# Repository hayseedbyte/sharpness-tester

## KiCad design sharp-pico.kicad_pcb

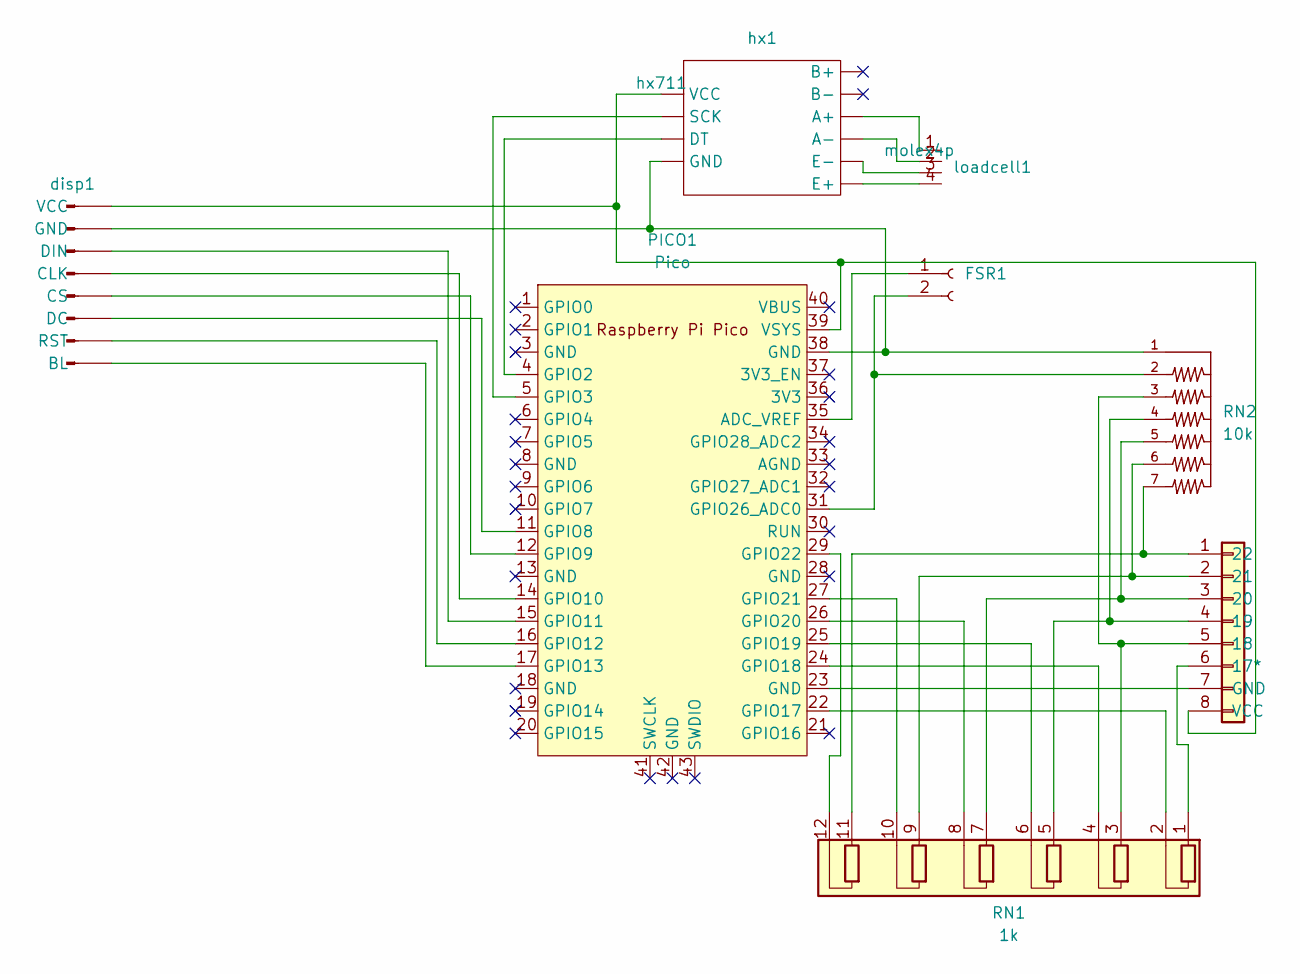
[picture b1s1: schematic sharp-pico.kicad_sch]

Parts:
CNTRL1: Conn_01x08; Molex_KK-254_AE-6410-08A_1x08_P2.54mm_Vertical
FSR1: Conn_01x02_Socket; PinSocket_1x02_P2.54mm_Vertical
PICO1: Pico; RPi_Pico_SMD_TH
RN1: 1k; R_Array_SIP12
RN2: 10k; R_Array_SIP7; PARTREV 09/19
disp1: Conn_01x08_Pin; Molex_KK-254_AE-6410-08A_1x08_P2.54mm_Vertical
hx1: hx711
loadcell1: molex4p; Molex_KK-254_AE-6410-04A_1x04_P2.54mm_Vertical

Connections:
unnamed: CNTRL1.6 (17*), RN1.1 (R1.1)
unnamed: CNTRL1.5 (18), RN1.3 (R2.1), RN2.3
unnamed: CNTRL1.4 (19), RN1.5 (R3.1), RN2.4
unnamed: CNTRL1.3 (20), RN1.7 (R4.1), RN2.5
unnamed: CNTRL1.2 (21), RN1.9 (R5.1), RN2.6
unnamed: CNTRL1.1 (22), RN1.11 (R6.1), RN2.7
unnamed: CNTRL1.7 (GND), PICO1.23 (GND)
unnamed: CNTRL1.8 (VCC), PICO1.39 (VSYS), disp1.1 (VCC), hx1.7 (VCC)
unnamed: FSR1.1, PICO1.35 (ADC_VREF)
unnamed: FSR1.2, PICO1.31 (GPIO26_ADC0), RN2.2
unnamed: PICO1.4 (GPIO2), hx1.9 (DT)
unnamed: PICO1.5 (GPIO3), hx1.8 (SCK)
unnamed: PICO1.11 (GPIO8), disp1.6 (DC)
unnamed: PICO1.12 (GPIO9), disp1.5 (CS)
unnamed: PICO1.14 (GPIO10), disp1.4 (CLK)
unnamed: PICO1.15 (GPIO11), disp1.3 (DIN)
unnamed: PICO1.16 (GPIO12), disp1.7 (RST)
unnamed: PICO1.17 (GPIO13), disp1.8 (BL)
unnamed: PICO1.22 (GPIO17), RN1.2 (R1.2)
unnamed: PICO1.24 (GPIO18), RN1.4 (R2.2)
unnamed: PICO1.25 (GPIO19), RN1.6 (R3.2)
unnamed: PICO1.26 (GPIO20), RN1.8 (R4.2)
unnamed: PICO1.27 (GPIO21), RN1.10 (R5.2)
unnamed: PICO1.29 (GPIO22), RN1.12 (R6.2)
unnamed: PICO1.38 (GND), RN2.1, disp1.2 (GND), hx1.10 (GND)
unnamed: hx1.3 (A+), loadcell1.1
unnamed: hx1.4 (A-), loadcell1.2
unnamed: hx1.6 (E+), loadcell1.4
unnamed: hx1.5 (E-), loadcell1.3

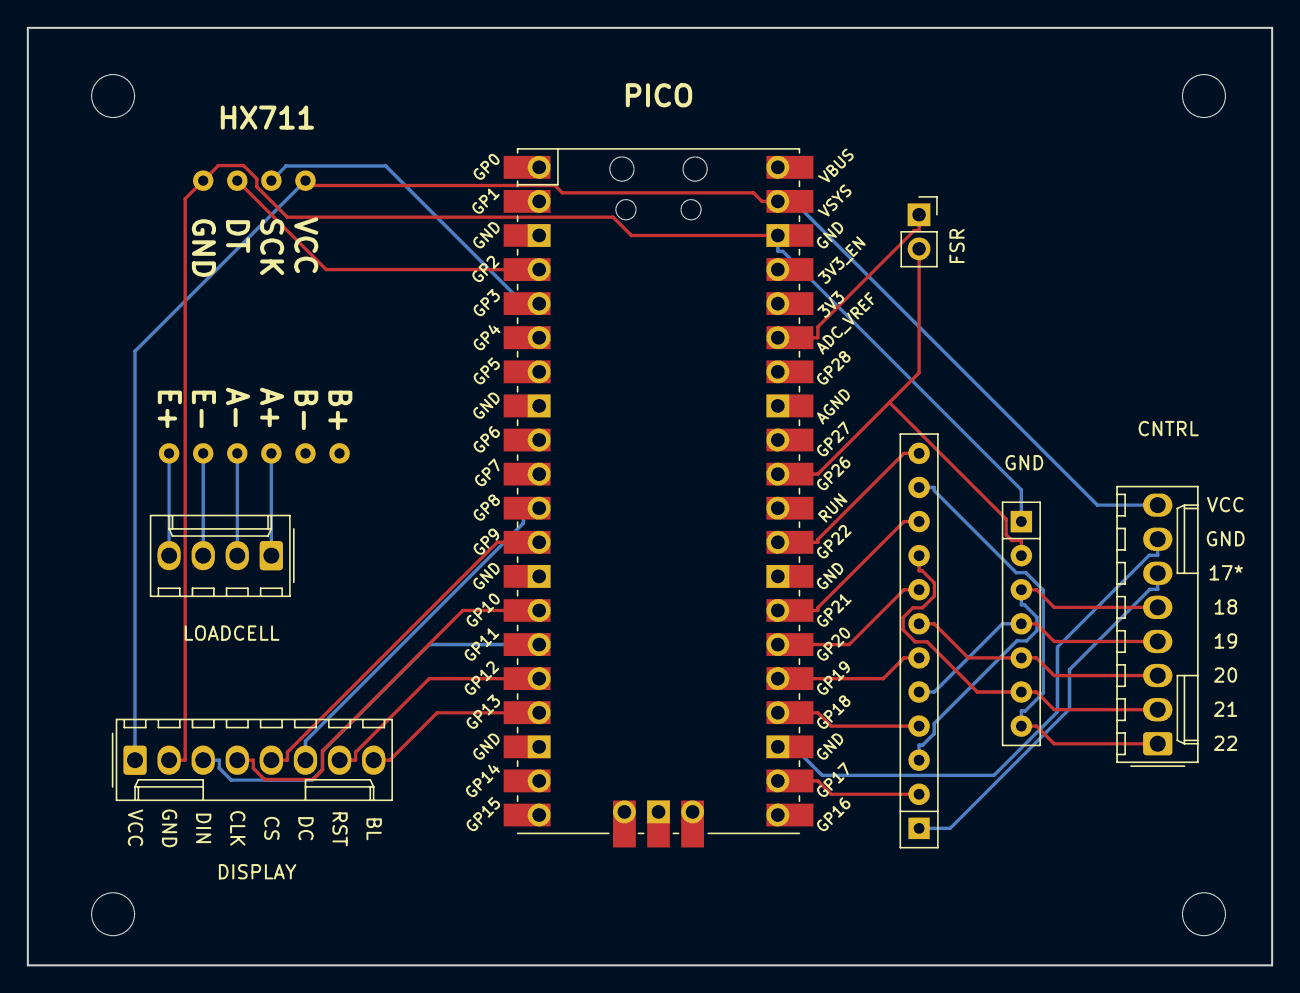
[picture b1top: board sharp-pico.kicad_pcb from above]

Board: 2 copper layers, 92.7 x 69.8 mm, 12 parts (0 on the bottom side), 29 nets.

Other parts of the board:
m1, m2, m3, m4: MountingHole_3.2mm_M3

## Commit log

2023-06-17 init
